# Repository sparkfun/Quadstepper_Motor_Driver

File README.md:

SparkFun QuadStepper Motor Driver Arduino Libary
================================================

[*SparkFun Quadstepper Motor Driver (ROB-10507)*](https://www.sparkfun.com/products/10507)

The Quadstepper motor driver board allows you to control up to 4 bipolar stepper motors simultaneously using logic level IO pins. 
Each motor driver has an output drive capacity of 35V and 1Amps. The board is capable of driving motors in full, half, quarter, eight, 
and sixteenth-step modes. The logic levels are selectable between 3.3V and 5V by way of a jumper. The bus header allows you to control 
all four motors with only 6 IO pins by controlling the enable (EN pins) for each motor, although each motor will be activated alone, not simultaneously. 
Be sure to close all of the ‘Bus Enable’ jumpers on the back of the board in order to use the Bus header.

Repository Contents
-------------------

* **/examples** - Example sketches for the library (.ino). Run these from the Arduino IDE. 
* **/src** - Source files for the library (.cpp, .h).
* **keywords.txt** - Keywords from this library that will be highlighted in the Arduino IDE. 
* **library.properties** - General library properties for the Arduino package manager. 

Documentation
--------------

* **[Installing an Arduino Library Guide](https://learn.sparkfun.com/tutorials/installing-an-arduino-library)** - Basic information on how to install an Arduino library.
* **[Quadstepper Github](https://github.com/sparkfun/Quadstepper_Motor_Driver)** - Main repository (including hardware files) for the SparkFun Quadstepper Motor Driver.

Products that use this Library 
---------------------------------

* [ROB-10507](https://www.sparkfun.com/products/10507)- SparkFun Quadstepper

License Information
-------------------

This product is _**open source**_! 

The **code** is beerware; if you see me (or any other SparkFun employee) at the local, and you've found our code helpful, please buy us a round!

Please use, reuse, and modify these files as you see fit. Please maintain attribution to SparkFun Electronics and release anything derivative under the same license.

Distributed as-is; no warranty is given.

- Your friends at SparkFun.

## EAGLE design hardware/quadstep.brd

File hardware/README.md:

quadstep
====

Cadsoft Eagle files.

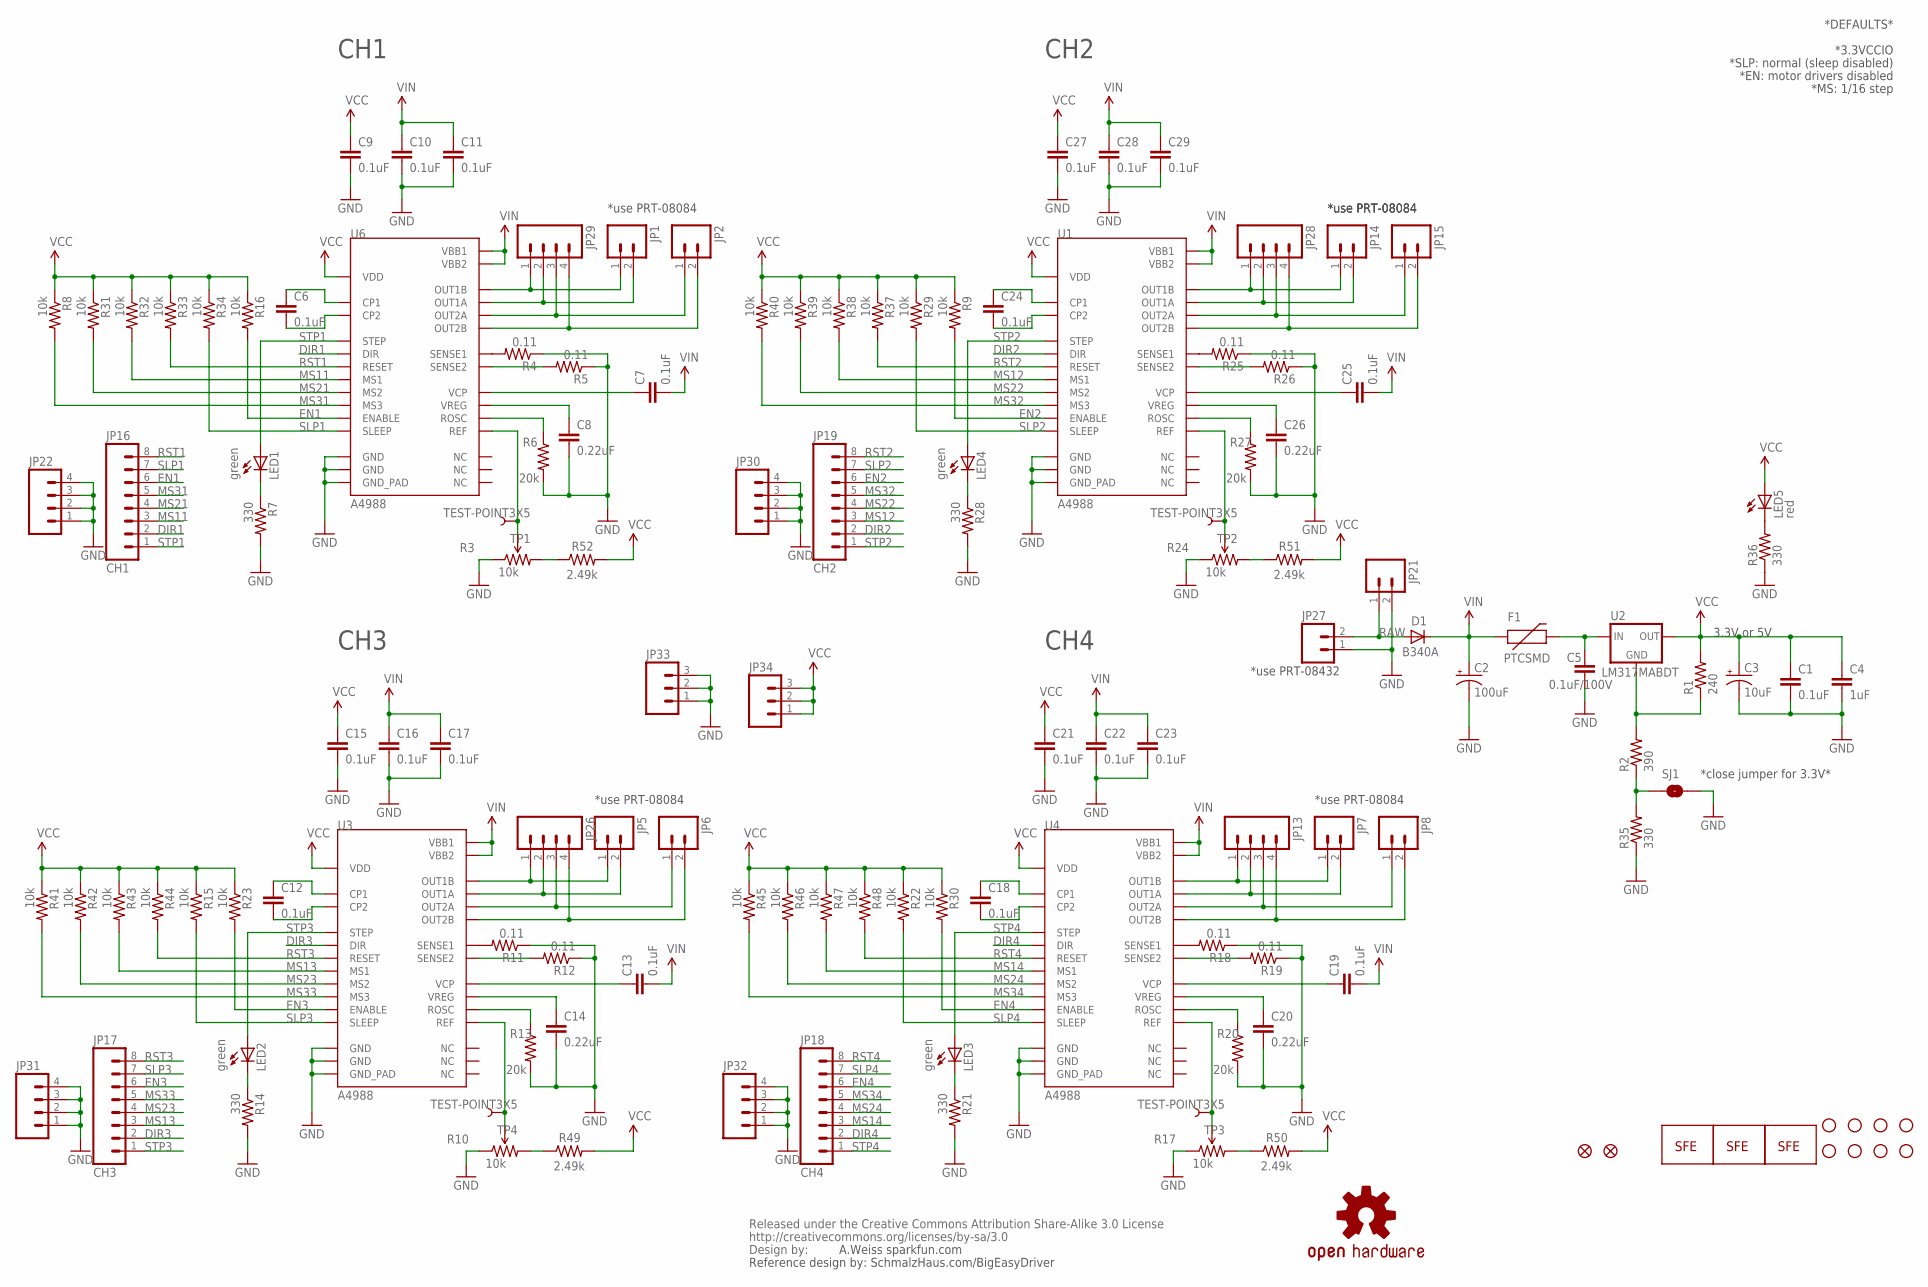
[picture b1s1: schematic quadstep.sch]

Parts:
C1, C6, C7, C9, C10, C11, C12, C13, C15, C16, C17, C18, C19, C21, C22, C23, C24, C25, C27, C28, C29: 0.1uF; 0402-CAP
C2: 100uF; PANASONIC_G
C3: 10uF; EIA3216
C4: 1uF; 0805
C5: 0.1uF/100V; 0402-CAP
C8, C14, C20, C26: 0.22uF; 0402-CAP
CC_TEXT1: CREATIVE_COMMONS
D1: B340A; SMA-DIODE
F1: PTCSMD; PTC-1206
JP1, JP2, JP5, JP6, JP7, JP8, JP14, JP15: M023.5MM_LOCK; SCREWTERMINAL-3.5MM-2_LOCK
JP9, JP10, JP11, JP12: STAND-OFF
JP13, JP22, JP26, JP28, JP29, JP30, JP31, JP32: M04PTH; 1X04
JP16: CH1; 1X08
JP17: CH3; 1X08
JP18: CH4; 1X08
JP19: CH2; 1X08
JP20: LOGO-SFENEW; SFE-NEW-WEBLOGO
JP21: M025MM; SCREWTERMINAL-5MM-2
JP23: LOGO-SFESK; SFE-LOGO-FLAME
JP24, JP25: FIDUCIAL1X2; FIDUCIAL-1X2
JP27: M02PTH; 1X02
JP33, JP34: M03PTH; 1X03
LED1, LED2, LED3, LED4: green; LED-0603
LED5: red; LED-0603
LOGO1: LOGO-SFENW2; SFE-NEW-WEB
R1: 240; 0402-RES
R2: 390; 0402-RES
R3, R10, R17, R24: 10k; TRIMPOT-3MM
R4, R5, R11, R12, R18, R19, R25, R26: 0.11; R2010
R6, R13, R20, R27: 20k; 0402-RES
R7, R14, R21, R28, R35, R36: 330; 0402-RES
R8, R9, R15, R16, R22, R23, R29, R30, R31, R32, R33, R34, R37, R38, R39, R40, R41, R42, R43, R44, R45, R46, R47, R48: 10k; 0402-RES
R49, R50, R51, R52: 2.49k; 0402-RES
SJ1: SOLDERJUMPERNO; SJ_2S-NO
STANDOFF1, STANDOFF2, STANDOFF3, STANDOFF4: STAND-OFFTIGHT; STAND-OFF-TIGHT
TP1, TP2, TP3, TP4: TEST-POINT3X5; PAD.03X.05
U1, U3, U4, U6: A4988; QFN-28-5MM-1:1
U2: LM317MABDT; DPAK
U$1: OSHW-LOGOS; OSHW-LOGO-S

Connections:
DIR1: JP16.2, U6.P$19 (DIR)
DIR2: JP19.2, U1.P$19 (DIR)
DIR3: JP17.2, U3.P$19 (DIR)
DIR4: JP18.2, U4.P$19 (DIR)
EN1: JP16.6, R16.2, U6.P$2 (ENABLE)
EN2: JP19.6, R9.2, U1.P$2 (ENABLE)
EN3: JP17.6, R23.2, U3.P$2 (ENABLE)
EN4: JP18.6, R30.2, U4.P$2 (ENABLE)
GND: C1.2, C2.-, C3.C (-), C4.2, C5.2, C8.2, C9.2, C10.2, C11.2, C14.2, C15.2, C16.2, C17.2, C20.2, C21.2, C22.2, C23.2, C26.2, C27.2, C28.2, C29.2, JP21.2, JP22.1, JP22.2, JP22.3, JP22.4, JP27.1, JP30.1, JP30.2, JP30.3, JP30.4, JP31.1, JP31.2, JP31.3, JP31.4, JP32.1, JP32.2, JP32.3, JP32.4, JP33.1, JP33.2, JP33.3, R3.1 (CCW), R4.1, R5.1, R6.2, R7.2, R10.1 (CCW), R11.1, R12.1, R13.2, R14.2, R17.1 (CCW), R18.1, R19.1, R20.2, R21.2, R24.1 (CCW), R25.1, R26.1, R27.2, R28.2, R35.1, R36.1, SJ1.2, U1.P$3 (GND), U1.P$18 (GND), U1.P$29 (GND_PAD), U3.P$3 (GND), U3.P$18 (GND), U3.P$29 (GND_PAD), U4.P$3 (GND), U4.P$18 (GND), U4.P$29 (GND_PAD), U6.P$3 (GND), U6.P$18 (GND), U6.P$29 (GND_PAD)
MS11: JP16.3, R32.2, U6.P$9 (MS1)
MS12: JP19.3, R38.2, U1.P$9 (MS1)
MS13: JP17.3, R43.2, U3.P$9 (MS1)
MS14: JP18.3, R47.2, U4.P$9 (MS1)
MS21: JP16.4, R31.2, U6.P$10 (MS2)
MS22: JP19.4, R39.2, U1.P$10 (MS2)
MS23: JP17.4, R42.2, U3.P$10 (MS2)
MS24: JP18.4, R46.2, U4.P$10 (MS2)
MS31: JP16.5, R8.2, U6.P$11 (MS3)
MS32: JP19.5, R40.2, U1.P$11 (MS3)
MS33: JP17.5, R41.2, U3.P$11 (MS3)
MS34: JP18.5, R45.2, U4.P$11 (MS3)
unnamed: R1.1, R2.2, U2.1 (GND)
unnamed: JP7.1, JP13.1, U4.P$21 (OUT1B)
unnamed: JP1.2, JP29.2, U6.P$24 (OUT1A)
unnamed: C5.1, F1.2, U2.3 (IN)
unnamed: JP5.1, JP26.1, U3.P$21 (OUT1B)
unnamed: JP2.1, JP29.3, U6.P$26 (OUT2A)
unnamed: JP2.2, JP29.4, U6.P$1 (OUT2B)
unnamed: R25.2, U1.P$23 (SENSE1)
unnamed: R5.2, U6.P$27 (SENSE2)
unnamed: C7.1, U6.P$6 (VCP)
unnamed: C8.1, U6.P$8 (VREG)
unnamed: R6.1, U6.P$13 (ROSC)
unnamed: C6.1, U6.P$4 (CP1)
unnamed: R3.2 (WIPER), TP1.P$1, U6.P$17 (REF)
unnamed: C6.2, U6.P$5 (CP2)
unnamed: LED1.C, R7.1
unnamed: R12.2, U3.P$27 (SENSE2)
unnamed: C13.1, U3.P$6 (VCP)
unnamed: C14.1, U3.P$8 (VREG)
unnamed: R13.1, U3.P$13 (ROSC)
unnamed: R10.2 (WIPER), TP4.P$1, U3.P$17 (REF)
unnamed: C12.1, U3.P$4 (CP1)
unnamed: R2.1, R35.2, SJ1.1
unnamed: C12.2, U3.P$5 (CP2)
unnamed: LED2.C, R14.1
unnamed: LED5.C, R36.2
unnamed: R10.3 (CW), R49.1
unnamed: JP5.2, JP26.2, U3.P$24 (OUT1A)
unnamed: JP6.1, JP26.3, U3.P$26 (OUT2A)
unnamed: JP6.2, JP26.4, U3.P$1 (OUT2B)
unnamed: R19.2, U4.P$27 (SENSE2)
unnamed: C19.1, U4.P$6 (VCP)
unnamed: C20.1, U4.P$8 (VREG)
unnamed: R20.1, U4.P$13 (ROSC)
unnamed: R17.2 (WIPER), TP3.P$1, U4.P$17 (REF)
unnamed: C18.1, U4.P$4 (CP1)
unnamed: C18.2, U4.P$5 (CP2)
unnamed: LED3.C, R21.1
unnamed: JP14.1, JP28.1, U1.P$21 (OUT1B)
unnamed: JP7.2, JP13.2, U4.P$24 (OUT1A)
unnamed: JP8.1, JP13.3, U4.P$26 (OUT2A)
unnamed: JP8.2, JP13.4, U4.P$1 (OUT2B)
unnamed: R26.2, U1.P$27 (SENSE2)
unnamed: C25.1, U1.P$6 (VCP)
unnamed: C26.1, U1.P$8 (VREG)
unnamed: R27.1, U1.P$13 (ROSC)
unnamed: R24.2 (WIPER), TP2.P$1, U1.P$17 (REF)
unnamed: C24.1, U1.P$4 (CP1)
unnamed: C24.2, U1.P$5 (CP2)
unnamed: LED4.C, R28.1
unnamed: JP1.1, JP29.1, U6.P$21 (OUT1B)
unnamed: JP14.2, JP28.2, U1.P$24 (OUT1A)
unnamed: JP15.1, JP28.3, U1.P$26 (OUT2A)
unnamed: JP15.2, JP28.4, U1.P$1 (OUT2B)
unnamed: R17.3 (CW), R50.1
unnamed: R24.3 (CW), R51.1
unnamed: R3.3 (CW), R52.1
unnamed: R4.2, U6.P$23 (SENSE1)
unnamed: R11.2, U3.P$23 (SENSE1)
unnamed: R18.2, U4.P$23 (SENSE1)
RAW: D1.A, JP21.1, JP27.2
RST1: JP16.8, R33.2, U6.P$12 (RESET)
RST2: JP19.8, R37.2, U1.P$12 (RESET)
RST3: JP17.8, R44.2, U3.P$12 (RESET)
RST4: JP18.8, R48.2, U4.P$12 (RESET)
SLP1: JP16.7, R34.2, U6.P$14 (SLEEP)
SLP2: JP19.7, R29.2, U1.P$14 (SLEEP)
SLP3: JP17.7, R15.2, U3.P$14 (SLEEP)
SLP4: JP18.7, R22.2, U4.P$14 (SLEEP)
STP1: JP16.1, LED1.A, U6.P$16 (STEP)
STP2: JP19.1, LED4.A, U1.P$16 (STEP)
STP3: JP17.1, LED2.A, U3.P$16 (STEP)
STP4: JP18.1, LED3.A, U4.P$16 (STEP)
VCC: C1.1, C3.A (+), C4.1, C9.1, C15.1, C21.1, C27.1, JP34.1, JP34.2, JP34.3, LED5.A, R1.2, R8.1, R9.1, R15.1, R16.1, R22.1, R23.1, R29.1, R30.1, R31.1, R32.1, R33.1, R34.1, R37.1, R38.1, R39.1, R40.1, R41.1, R42.1, R43.1, R44.1, R45.1, R46.1, R47.1, R48.1, R49.2, R50.2, R51.2, R52.2, U1.P$15 (VDD), U2.4 (OUT), U3.P$15 (VDD), U4.P$15 (VDD), U6.P$15 (VDD)
VIN: C2.+, C7.2, C10.1, C11.1, C13.2, C16.1, C17.1, C19.2, C22.1, C23.1, C25.2, C28.1, C29.1, D1.C, F1.1, U1.P$22 (VBB1), U1.P$28 (VBB2), U3.P$22 (VBB1), U3.P$28 (VBB2), U4.P$22 (VBB1), U4.P$28 (VBB2), U6.P$22 (VBB1), U6.P$28 (VBB2)

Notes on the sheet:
CH1
CH2
CH3
CH4
*DEFAULTS*
*MS: 1/16 step
*3.3VCCIO
*close jumper for 3.3V*
*EN: motor drivers disabled
*SLP: normal (sleep disabled)
A.Weiss sparkfun.com
Reference design by: SchmalzHaus.com/BigEasyDriver
3.3V or 5V
*use PRT-08432
*use PRT-08084

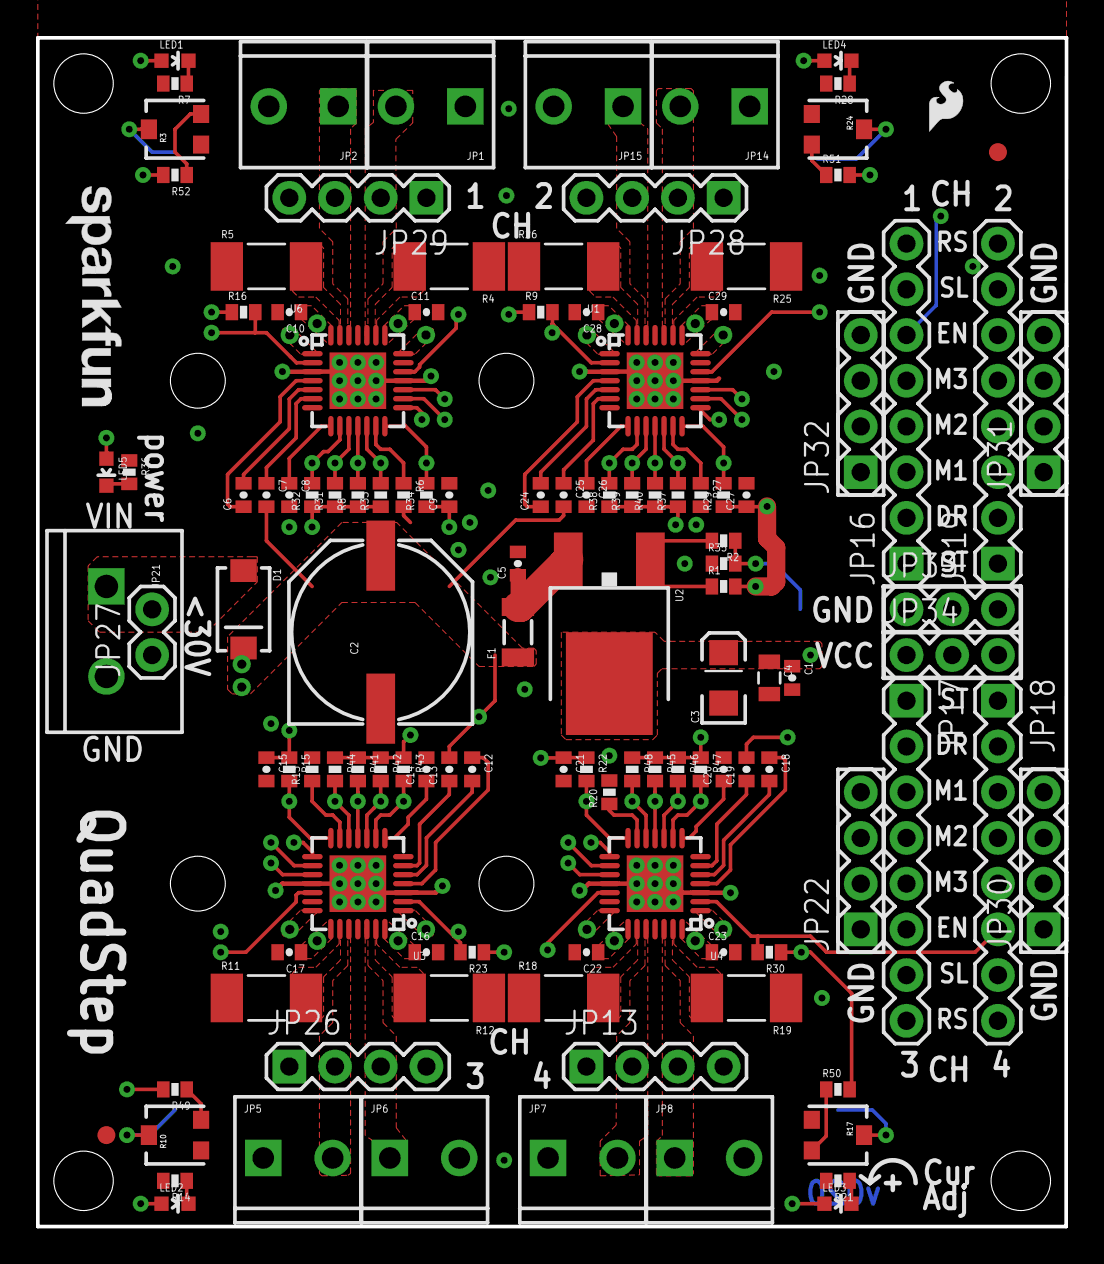
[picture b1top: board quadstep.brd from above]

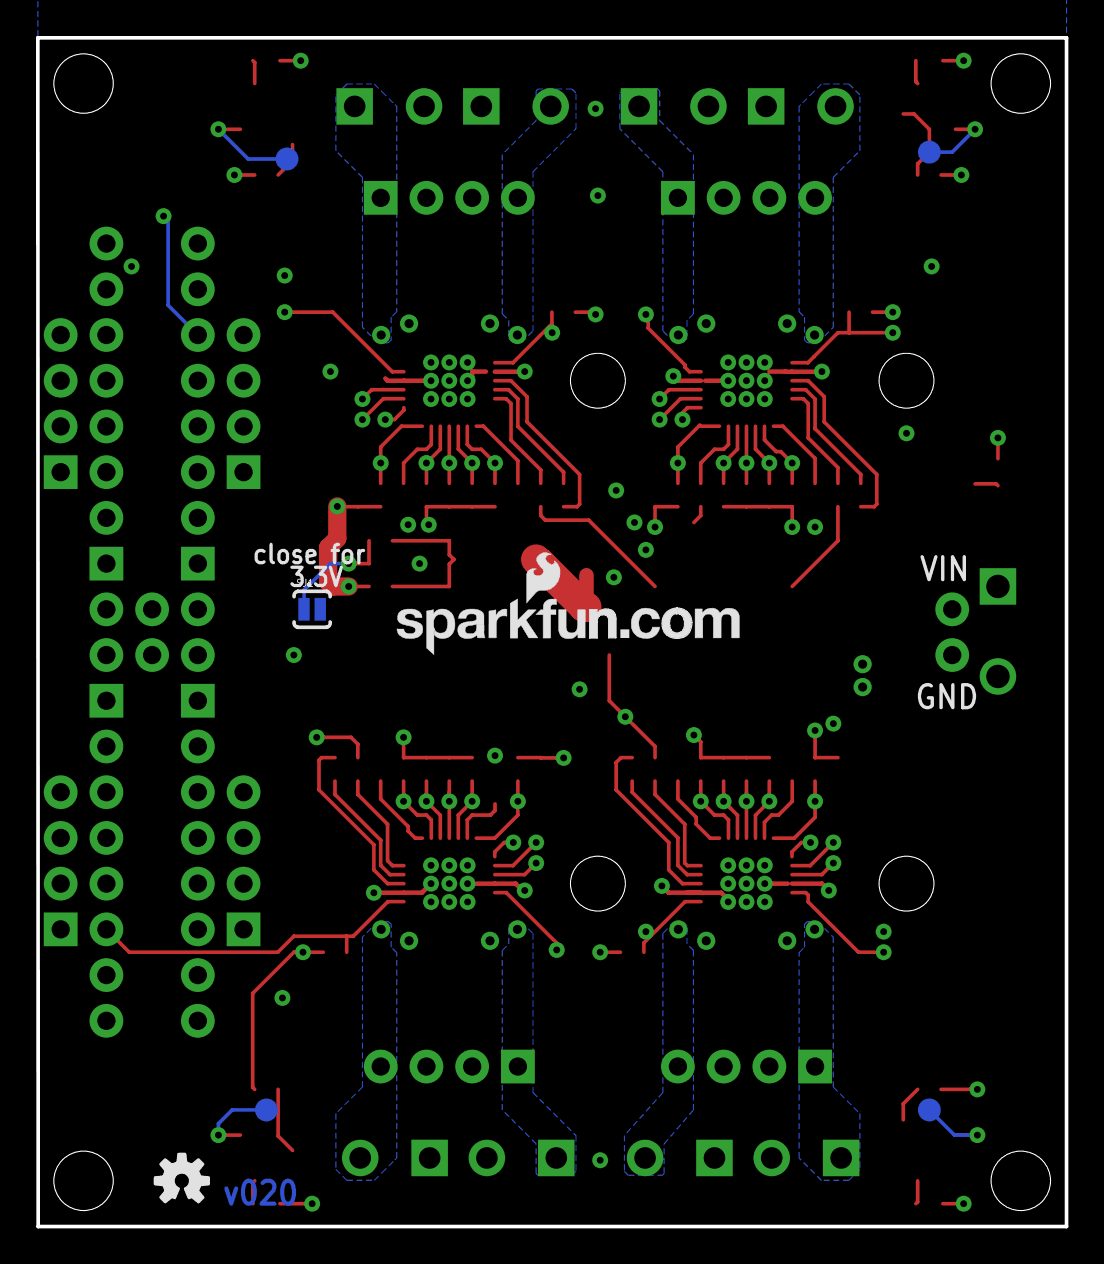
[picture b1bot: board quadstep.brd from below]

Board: 4 copper layers, 57.1 x 66.0 mm, 137 parts (7 on the bottom side), 96 nets.

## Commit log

2013-01-28 added files
2013-01-28 added readmes
2013-02-01 prototype v020
2013-02-04 v020 proto
    -added standoffs for heatsinks
    -changed A4988 FP
2015-01-19 Updating README and adding in Arduino libraries
2015-01-19 Updating to current board files
2015-01-19 Fixing GitHub file directory weirdness
2015-01-19 Adding back in hardware files
2015-04-24 Squashed 'Libraries/Arduino/' content from commit 8feeb15
    git-subtree-dir: Libraries/Arduino
    git-subtree-split: 8feeb151bedc8d5ba55fc6744196e73500bd2357
2015-04-24 Changed structure for Library Manager changes.
2015-05-07 Squashed 'Libraries/Arduino/' changes from 8feeb15..45fd100
    git-subtree-dir: Libraries/Arduino
    git-subtree-split: 45fd1007f1f4302c1e057c1e230df1cb51fb9a41
2015-05-07 Updating subtree directions for library

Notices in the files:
parts and their libraries:
SparkFun-Aesthetics: Licensing: CC v3.0 Share-Alike You are welcome to use this library for commercial purposes.
SparkFun-Aesthetics: Released under the Creative Commons Attribution Share-Alike 3.0 License
SparkFun-Aesthetics: http://creativecommons.org/licenses/by-sa/3.0
